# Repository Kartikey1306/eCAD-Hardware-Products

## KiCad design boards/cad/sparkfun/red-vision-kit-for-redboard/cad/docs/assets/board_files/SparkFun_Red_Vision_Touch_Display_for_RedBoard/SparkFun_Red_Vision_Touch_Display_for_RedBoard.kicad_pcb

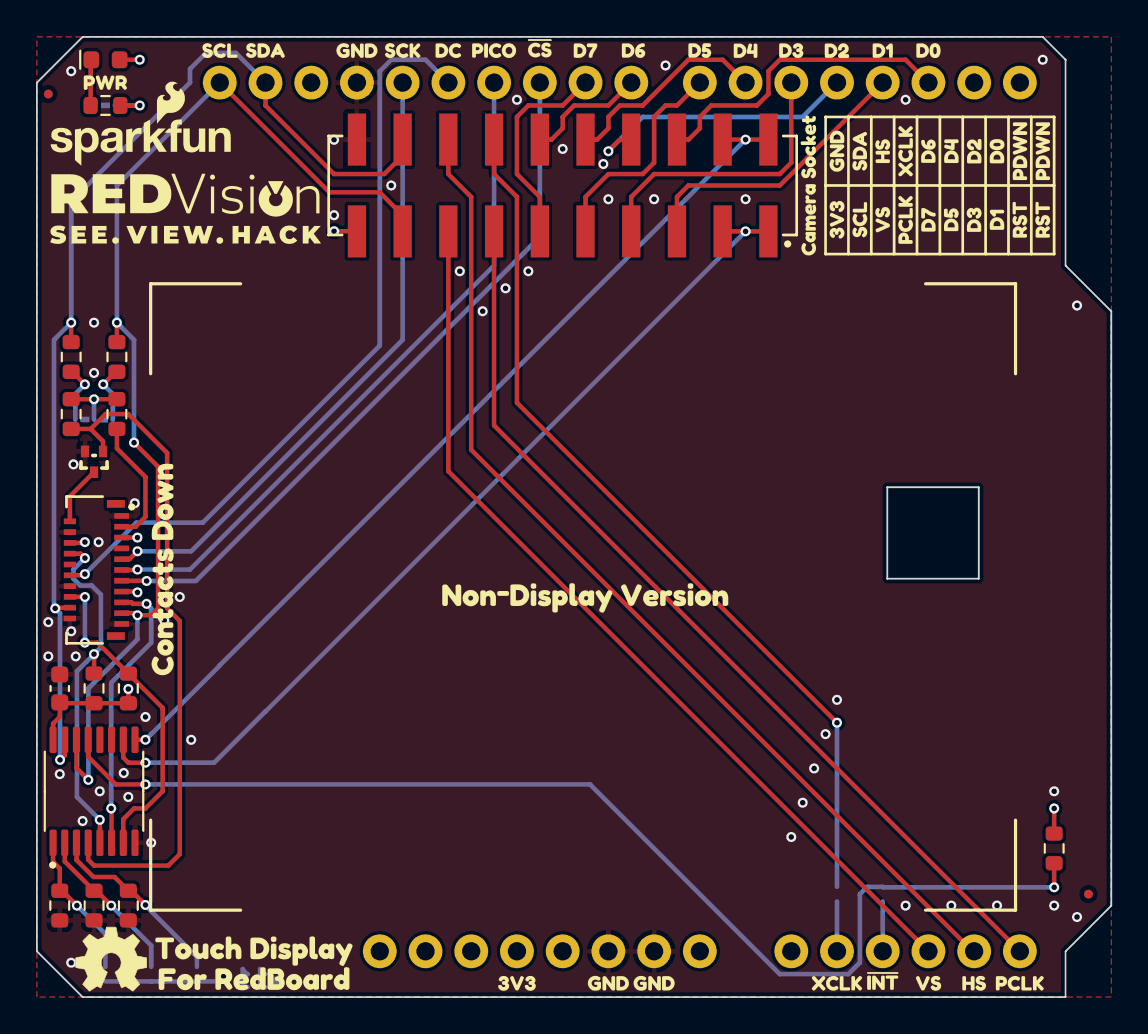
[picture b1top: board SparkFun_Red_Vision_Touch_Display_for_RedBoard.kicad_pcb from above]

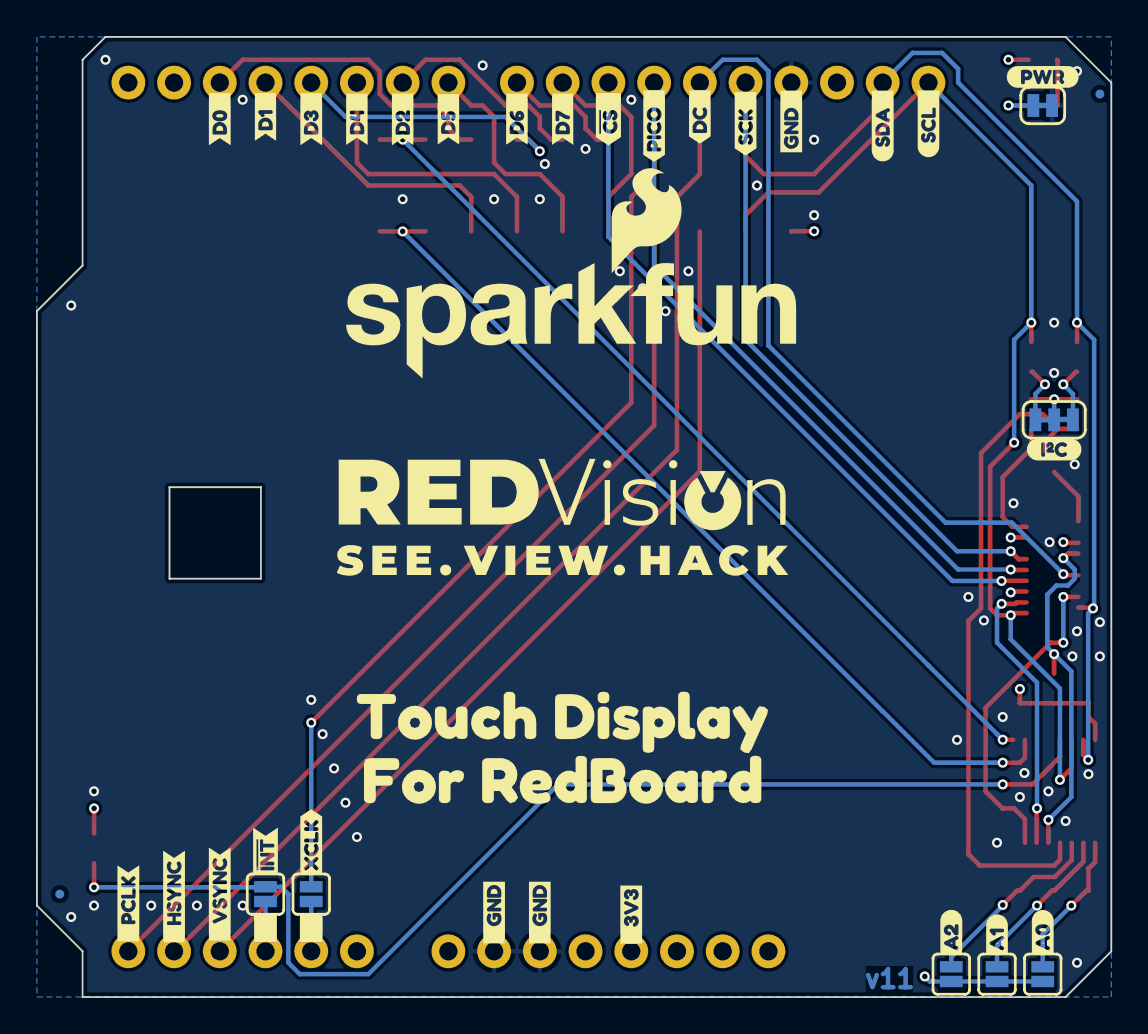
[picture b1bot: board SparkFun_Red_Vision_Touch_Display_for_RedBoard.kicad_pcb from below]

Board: 4 copper layers, 59.7 x 53.3 mm, 111 parts (39 on the bottom side), 38 nets.

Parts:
B1: Arduino_Uno_R3_Shield; Uno_R3_Shield_NoLabels
C2: 0.1uF; C_0603_1608Metric
D1: Red; LED_0603_1608Metric_Red
FID1, FID2, FID3, FID4: Fiducial_0.5mm; Fiducial_0.5mm_Mask1mm
G3: OSHW_Logo; Creative_Commons_License
J1: Conn_02x10_2.54mm_SMD; 2x10_P2.54mm_Socket_Vertical_SMD
J4: Conn_01x21_FPC; FPC_1x21_P0.3mm_Horizontal_DualContact
JP1: I2C; Jumper_3_NC-2_Trace
JP13: XCLK; Jumper_2_NO
JP14: A0; Jumper_2_NO
JP15: A1; Jumper_2_NO
JP16: A2; Jumper_2_NO
JP21: PWR; Jumper_2_NC_Trace
JP22: ~{INT}; Jumper_2_NO
Q1: RE1C002UNTCL; SC-89 SOT-490
R1: 10; R_0603_1608Metric
R2, R6, R7, R8, R9, R11, R12: 100k; R_0603_1608Metric
R3, R4: 2.2k; R_0603_1608Metric
R5: 4.7k; R_0603_1608Metric
Ref**: Val**; OSHW_Logo_4mm
U1: 2" LCD-TFT 240x320; LCD_TFT_2.0in_Waveshare_Outline
U2: PCA9534PW; TSSOP-16_4.4x5mm_P0.65mm
kibuzzard-67A69C5F, kibuzzard-67A69C5F#2: G***; kibuzzard-67A69C5F
kibuzzard-67A69CD2, kibuzzard-67A69CD2#2: G***; kibuzzard-67A69CD2
kibuzzard-67A69CDC: G***; kibuzzard-67A69CDC
kibuzzard-67A69CE2: G***; kibuzzard-67A69CE2
kibuzzard-67A69CE6: G***; kibuzzard-67A69CE6
kibuzzard-67A69CEA: G***; kibuzzard-67A69CEA
kibuzzard-67A69CFF: G***; kibuzzard-67A69CFF
kibuzzard-67A69D0C: G***; kibuzzard-67A69D0C
kibuzzard-67A69D0F: G***; kibuzzard-67A69D0F
kibuzzard-67A69D1B: G***; kibuzzard-67A69D1B
kibuzzard-67A69D2C: G***; kibuzzard-67A69D2C
kibuzzard-67A69D2F: G***; kibuzzard-67A69D2F
kibuzzard-67A69D05: G***; kibuzzard-67A69D05
kibuzzard-67A69D16: G***; kibuzzard-67A69D16
kibuzzard-67A69D28: G***; kibuzzard-67A69D28
kibuzzard-67A69D32: G***; kibuzzard-67A69D32
kibuzzard-67A69E51: G***; kibuzzard-67A69E51
kibuzzard-67A69E55: G***; kibuzzard-67A69E55
kibuzzard-67B3FFE0: G***; kibuzzard-67B3FFE0
kibuzzard-67C124A5: G***; kibuzzard-67C124A5
kibuzzard-67C1248C: G***; kibuzzard-67C1248C
kibuzzard-68B0C822: G***; kibuzzard-68B0C822
kibuzzard-68B0C855: G***; kibuzzard-68B0C855
kibuzzard-68B1DD36: G***; kibuzzard-68B1DD36
kibuzzard-68B9B772: G***; kibuzzard-68B9B772
kibuzzard-68B9BC57: G***; kibuzzard-68B9BC57
kibuzzard-68B9BC59: G***; kibuzzard-68B9BC59
kibuzzard-68B9BC63: G***; kibuzzard-68B9BC63
kibuzzard-68B9BCE4: G***; kibuzzard-68B9BCE4
kibuzzard-68B9BCEA: G***; kibuzzard-68B9BCEA
kibuzzard-68B9BCF4: G***; kibuzzard-68B9BCF4
kibuzzard-68B9BD3D: G***; kibuzzard-68B9BD3D
kibuzzard-68B9BD4B: G***; kibuzzard-68B9BD4B
kibuzzard-68B9BD7F: G***; kibuzzard-68B9BD7F
kibuzzard-68B9BD9B: G***; kibuzzard-68B9BD9B
kibuzzard-68B9BD55: G***; kibuzzard-68B9BD55
kibuzzard-68B9BD76: G***; kibuzzard-68B9BD76
kibuzzard-68B9BDA0: G***; kibuzzard-68B9BDA0
kibuzzard-68B9BDA7: G***; kibuzzard-68B9BDA7
kibuzzard-68B9BDC0: G***; kibuzzard-68B9BDC0
kibuzzard-68B9BDC6: G***; kibuzzard-68B9BDC6
kibuzzard-68B9BDCB: G***; kibuzzard-68B9BDCB
kibuzzard-68B9BE6E: G***; kibuzzard-68B9BE6E
kibuzzard-68B9BE9E: G***; kibuzzard-68B9BE9E
kibuzzard-68B9BE85: G***; kibuzzard-68B9BE85
kibuzzard-68B9BE89: G***; kibuzzard-68B9BE89
kibuzzard-68B9BEAF: G***; kibuzzard-68B9BEAF
kibuzzard-68B9BECE, kibuzzard-68B9BECE#2: G***; kibuzzard-68B9BECE
kibuzzard-68B9BED6: G***; kibuzzard-68B9BED6
kibuzzard-68B9BEDF: G***; kibuzzard-68B9BEDF
kibuzzard-68B9BEFF: G***; kibuzzard-68B9BEFF
kibuzzard-68B9BF01: G***; kibuzzard-68B9BF01
kibuzzard-68B9BF2B: G***; kibuzzard-68B9BF2B
kibuzzard-68B9BF3C: G***; kibuzzard-68B9BF3C
kibuzzard-68B9BF4D: G***; kibuzzard-68B9BF4D
kibuzzard-68B9BF5D: G***; kibuzzard-68B9BF5D
kibuzzard-68B9BF06: G***; kibuzzard-68B9BF06
kibuzzard-68B9BF8B: G***; kibuzzard-68B9BF8B
kibuzzard-68B9BF11: G***; kibuzzard-68B9BF11
kibuzzard-68B9BF14: G***; kibuzzard-68B9BF14
kibuzzard-68B9BF19: G***; kibuzzard-68B9BF19
kibuzzard-68B9BF49: G***; kibuzzard-68B9BF49
kibuzzard-68B9BF52: G***; kibuzzard-68B9BF52
kibuzzard-68B9BF61: G***; kibuzzard-68B9BF61
kibuzzard-68B9BF65: G***; kibuzzard-68B9BF65
kibuzzard-68B9BF69: G***; kibuzzard-68B9BF69
kibuzzard-68B202D3: G***; kibuzzard-68B202D3
kibuzzard-68B202D8: G***; kibuzzard-68B202D8
kibuzzard-68EEA4F5: G***; kibuzzard-68EEA4F5
kibuzzard-68EEA4FB: G***; kibuzzard-68EEA4FB
kibuzzard-68EEA50D: G***; kibuzzard-68EEA50D
kibuzzard-68EEA51B: G***; kibuzzard-68EEA51B
kibuzzard-68EEA508: G***; kibuzzard-68EEA508
kibuzzard-68EEA511: G***; kibuzzard-68EEA511
kibuzzard-68EEA516: G***; kibuzzard-68EEA516
kibuzzard-68EEA520: G***; kibuzzard-68EEA520

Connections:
3.3V: B1.3.3V, C2.1, D1.2 (A), J1.19, J4.5, J4.6, J4.15, JP1.2 (B), JP14.2 (B), JP15.2 (B), JP16.2 (B), R1.2, R2.2, R6.2, R11.2, R12.2, U2.16 (VDD)
A0: JP14.1 (A), R7.2, U2.1 (A0)
A1: JP15.1 (A), R8.2, U2.2 (A1)
A2: JP16.1 (A), R9.2, U2.3 (A2)
CAM_D0: B1.D2, J1.6
CAM_D1: B1.D3 (*D3), J1.5
CAM_D2: B1.D4, J1.8
CAM_D3: B1.D5 (*D5), J1.7
CAM_D4: B1.D6 (*D6), J1.10
CAM_D5: B1.D7, J1.9
CAM_D6: B1.D8, J1.12
CAM_D7: B1.D9 (*D9), J1.11
CAM_HS: B1.A4, J1.16
CAM_PCLK: B1.A5, J1.13
CAM_PWDN: J1.2, J1.4, U2.9 (IO4)
CAM_RST: J1.1, J1.3, U2.10 (IO5)
CAM_VS: B1.A3, J1.15
CAM_XCLK: J1.14, JP13.1 (A)
DISP_BL: Q1.1 (G), R2.1, U2.4 (IO0)
DISP_~CS: B1.D10 (*D10), J4.13
DISP_~RST: J4.8, R12.1, U2.5 (IO1)
GND: B1.GND, C2.2, J1.20, J4.1, J4.4, J4.7, J4.14, J4.20, J4.21, JP21.2 (B), Q1.2 (S), R7.1, R8.1, R9.1, U2.8 (VSS)
unnamed: D1.1 (K), R5.2
unnamed: J4.2, Q1.3 (D)
unnamed: J4.3, R1.1
unnamed: JP1.1 (A), R4.1
unnamed: JP1.3 (C), R3.2
unnamed: B1.A1, JP13.2 (B)
unnamed: JP21.1 (A), R5.1
unnamed: B1.A2, JP22.2 (B)
PICO: B1.D11 (*D11/PICO), J4.11
POCI/DC: B1.D12 (D12/POCI), J4.12
SCK: B1.D13 (D13/SCK), J4.9
SCL: B1.SCL, J1.17, J4.19, R4.2, U2.14 (SCL)
SDA: B1.SDA, J1.18, J4.18, R3.1, U2.15 (SDA)
TP_INT: J4.17, U2.6 (IO2)
TP_~RST: J4.16, R11.1, U2.7 (IO3)
~INT: JP22.1 (A), R6.1, U2.13 (~INT)

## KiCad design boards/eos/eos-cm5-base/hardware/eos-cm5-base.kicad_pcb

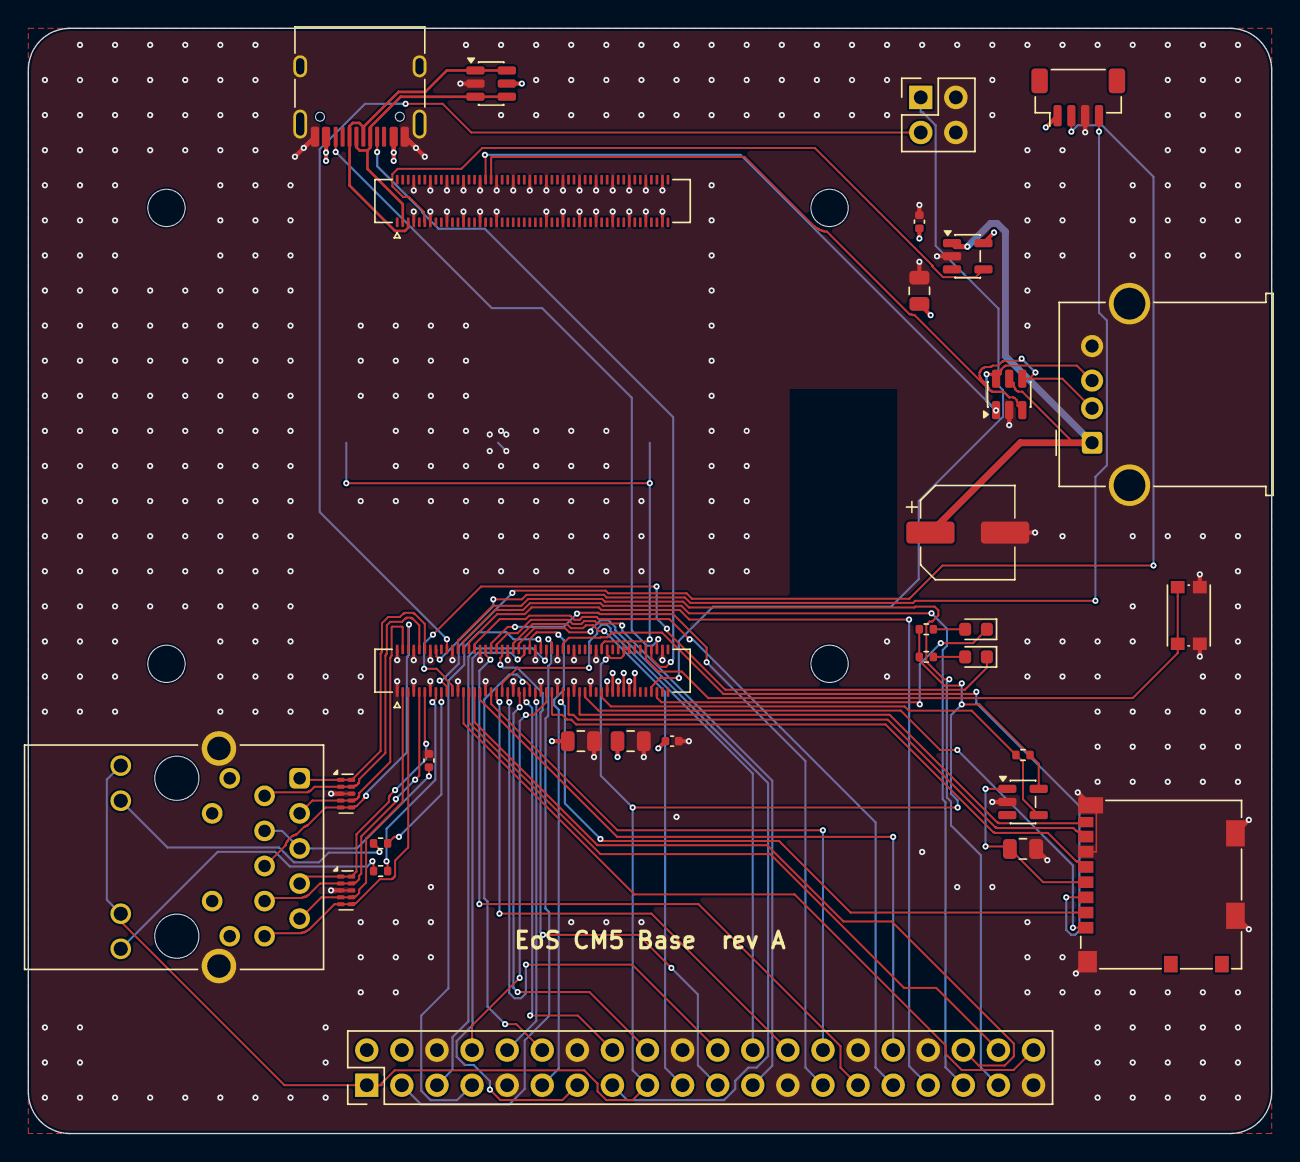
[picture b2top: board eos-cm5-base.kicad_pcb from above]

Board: 4 copper layers, 90.0 x 80.0 mm, 36 parts (1 on the bottom side), 70 nets.

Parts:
BT1: CR2032; BatteryHolder_Keystone_3034_1x20mm
C1, C2, C5, C8: 10u; C_0805_2012Metric
C3, C4, C7: 100n; C_0402_1005Metric
C6: 150u; CP_Elec_6.3x5.8
D1: PWR; LED_0603_1608Metric
D2: ACT; LED_0603_1608Metric
H1, H2, H3, H4: M2.5; MountingHole_2.7mm_M2.5
J1: CM5 1-100; Hirose_DF40C-100DS-0.4V_2x50_P0.4mm
J2: CM5 101-200; Hirose_DF40C-100DS-0.4V_2x50_P0.4mm
J3: USB-C; USB_C_Receptacle_HRO_TYPE-C-31-M-12
J4: USB-A; USB_A_Molex_67643_Horizontal
J5: TRJG0926HENL; TRXCOM_TRJG0926HENL
J6: microSD; microSD_HC_Molex_104031-0811
J7: GPIO; PinHeader_2x20_P2.54mm_Vertical
J8: FAN; JST_SH_BM04B-SRSS-TB_1x04-1MP_P1.00mm_Vertical
J9: BOOT; PinHeader_2x02_P2.54mm_Vertical
R1, R2: 470; R_0402_1005Metric
R3: 10k; R_0402_1005Metric
R4, R5: 1k; R_0402_1005Metric
SW1: POWER; SW_Push_1P1T_NO_CK_KMR2
U1, U3: USBLC6-2SC6; SOT-23-6
U2: TPS2051C; SOT-23-5
U4, U5: TPD4EUSB30; USON-10_2.5x1.0mm_P0.5mm
U6: RT9742GGJ5; TSOT-23-5

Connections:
+3V3: J1.78, J1.84, J1.86, J5.15, J5.17, J7.1, J7.17, R3.2, R4.1, R5.1, U6.5
+5V: C1.1, C2.1, C3.1, C4.1, C5.1, J1.77, J1.79, J1.81, J1.83, J1.85, J1.87, J3.A4, J3.A9, J3.B4, J3.B9, J7.2, J7.4, J8.1, U1.5, U2.5
/CC1: J1.94, J3.A5
/CC2: J1.96, J3.B5
/EEPROM_NWP: J1.20, J9.3
/ETH_A_N: J1.10, J5.2, U4.2, U4.9
/ETH_A_P: J1.12, J5.1, U4.1, U4.10
/ETH_B_N: J1.6, J5.6, U4.5, U4.6
/ETH_B_P: J1.4, J5.3, U4.4, U4.7
/ETH_CT: C7.1, J5.4, J5.5
/ETH_C_N: J1.9, J5.8, U5.2, U5.9
/ETH_C_P: J1.11, J5.7, U5.1, U5.10
/ETH_D_N: J1.5, J5.10, U5.5, U5.6
/ETH_D_P: J1.3, J5.9, U5.4, U5.7
/ETH_LEDG_K: J5.18, R2.1
/ETH_LEDY_K: J5.16, R1.1
/ETH_NLED_ACT: J1.15, R2.2
/ETH_NLED_SPD: J1.17, R1.2
/FAN_PWM: J1.19, J8.2
/FAN_TACHO: J1.16, J8.4
/GPIO2: J1.58, J7.3
/GPIO3: J1.56, J7.5
/GPIO4: J1.54, J7.7
/GPIO5: J1.34, J7.29
/GPIO6: J1.30, J7.31
/GPIO7: J1.37, J7.26
/GPIO8: J1.39, J7.24
/GPIO9: J1.40, J7.21
/GPIO10: J1.44, J7.19
/GPIO11: J1.38, J7.23
/GPIO12: J1.31, J7.32
/GPIO13: J1.28, J7.33
/GPIO14: J1.55, J7.8
/GPIO15: J1.51, J7.10
/GPIO16: J1.29, J7.36
/GPIO17: J1.50, J7.11
/GPIO18: J1.49, J7.12
/GPIO19: J1.26, J7.35
/GPIO20: J1.27, J7.38
/GPIO21: J1.25, J7.40
/GPIO22: J1.46, J7.15
/GPIO23: J1.47, J7.16
/GPIO24: J1.45, J7.18
/GPIO25: J1.41, J7.22
/GPIO26: J1.24, J7.37
/GPIO27: J1.48, J7.13
/ID_SC: J1.35, J7.28
/ID_SD: J1.36, J7.27
/LED_ACT_A: D2.2, R5.2
/LED_NACT: D2.1, J1.21
/LED_NPWR: D1.1, J1.95
/LED_PWR_A: D1.2, R4.2
/NRPIBOOT: J1.93, J9.1
/PWR_BUTTON: J1.92, SW1.1
/SD_CLK: J1.57, J6.5
/SD_CMD: J1.62, J6.3
/SD_DAT0: J1.63, J6.7
/SD_DAT1: J1.67, J6.8
/SD_DAT2: J1.69, J6.1
/SD_DAT3: J1.61, J6.2
/SD_PWR_ON: J1.75, R3.1, U6.4
/SD_VDD: C8.1, J6.4, U6.1
/USBH_DM: J2.36, J4.2, U3.3, U3.4
/USBH_DP: J2.34, J4.3, U3.1, U3.6
/USBH_VBUS: C6.1, J4.1, U2.1, U3.5
/USB_N: J2.3, J3.A7, J3.B7, U1.3, U1.4
/USB_P: J2.5, J3.A6, J3.B6, U1.1, U1.6
/VBAT: BT1.1, J1.76
/VBUS_EN: J2.11, U2.4
GND: BT1.2, C1.2, C2.2, C3.2, C4.2, C5.2, C6.2, C7.2, C8.2, J1.1, J1.2, J1.7, J1.8, J1.13, J1.14, J1.22, J1.23, J1.32, J1.33, J1.42, J1.43, J1.52, J1.53, J1.59, J1.60, J1.65, J1.66, J1.71, J1.74, J1.98, J2.7, J2.8, J2.13, J2.14, J2.19, J2.20, J2.25, J2.26, J2.31, J2.32, J2.37, J2.38, J2.44, J2.50, J2.55, J2.56, J2.61, J2.62, J2.67, J2.68, J2.73, J2.74, J2.79, J2.80, J2.85, J2.86, J2.91, J2.92, J2.97, J2.98, J3.A1, J3.A12, J3.B1, J3.B12, J3.SH, J4.4, J4.SH, J5.19, J5.20, J6.6, J6.SH, J7.6, J7.9, J7.14, J7.20, J7.25, J7.30, J7.34, J7.39, J8.3, J9.2, J9.4, SW1.2, U1.2, U2.2, U3.2, U4.3, U4.8, U5.3, U5.8, U6.2

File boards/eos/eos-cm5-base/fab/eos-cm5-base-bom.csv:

"Refs","Value","Footprint","Manufacturer","MPN","Description","Qty","DNP"
"BT1","CR2032","Battery:BatteryHolder_Keystone_3034_1x20mm","Keystone","3034","Coin cell holder, RTC (VBAT); keep RTC charging off with a CR2032","1",""
"C1,C2,C5,C8","10u","Capacitor_SMD:C_0805_2012Metric","","","Capacitor 10 uF 10 V X5R 0805 (5 V at the module),Capacitor 10 uF 10 V X5R 0805 (TPS2051C input, 1-22 uF per TI),Capacitor 10 uF 10 V X5R 0805 (microSD supply, as CM5IO)","4",""
"C3,C4,C7","100n","Capacitor_SMD:C_0402_1005Metric","","","Capacitor 100 nF X7R 0402 (5 V at the module),Capacitor 100 nF X7R 0402 (MagJack centre tap, as CM5IO),Capacitor 100 nF X7R 0402 (TPS2051C input, as TI specifies)","3",""
"C6","150u","Capacitor_SMD:CP_Elec_6.3x5.8","Panasonic","EEE-FK1A151P","Capacitor 150 uF 10 V aluminium, 6.3 x 5.8 mm (USB host port: 120 uF minimum per TI)","1",""
"D1","PWR","LED_SMD:LED_0603_1608Metric","Kingbright","APTD1608LSURCK","LED red 0603, power (LED_nPWR)","1",""
"D2","ACT","LED_SMD:LED_0603_1608Metric","Kingbright","APTD1608LCGCK","LED green 570 nm 0603, activity (LED_nACT)","1",""
"J1","CM5 1-100","Connector_Hirose_DF40:Hirose_DF40C-100DS-0.4V_2x50_P0.4mm","Amphenol","10164227-1001A1RLF","CM5 connector, pins 1-100, 1.5 mm stacking","1",""
"J2","CM5 101-200","Connector_Hirose_DF40:Hirose_DF40C-100DS-0.4V_2x50_P0.4mm","Amphenol","10164227-1001A1RLF","CM5 connector, pins 101-200, 1.5 mm stacking","1",""
"J3","USB-C","Connector_USB:USB_C_Receptacle_HRO_TYPE-C-31-M-12","Korean Hroparts","TYPE-C-31-M-12","USB-C 2.0 receptacle (power in, USB device)","1",""
"J4","USB-A","Connector_USB:USB_A_Molex_67643_Horizontal","Molex","67643-0910","USB-A receptacle, USB 2.0 host","1",""
"J5","TRJG0926HENL","EoS_Connectors:TRXCOM_TRJG0926HENL","TRXCOM","TRJG0926HENL","RJ45 MagJack 10/100/1000, LEDs (pins as on Raspberry Pi's CM5IO)","1",""
"J6","microSD","Connector_Card:microSD_HC_Molex_104031-0811","Molex","104031-0811","microSD socket (CM5 Lite)","1",""
"J7","GPIO","Connector_PinHeader_2.54mm:PinHeader_2x20_P2.54mm_Vertical","","","Raspberry Pi 40-pin GPIO header","1",""
"J8","FAN","Connector_JST:JST_SH_BM04B-SRSS-TB_1x04-1MP_P1.00mm_Vertical","JST","BM04B-SRSS-TB","Fan: 1 5 V, 2 PWM, 3 GND, 4 tacho","1",""
"J9","BOOT","Connector_PinHeader_2.54mm:PinHeader_2x02_P2.54mm_Vertical","","","Jumpers: 1-2 nRPIBOOT (USB boot), 3-4 EEPROM write protect","1",""
"R1,R2","470","Resistor_SMD:R_0402_1005Metric","","","Resistor 470 ohm 1% 0402 (green LED, activity),Resistor 470 ohm 1% 0402 (yellow LED, speed)","2",""
"R3","10k","Resistor_SMD:R_0402_1005Metric","","","Resistor 10 kohm 1% 0402 (SD_PWR_ON pull-up, as CM5IO)","1",""
"R4,R5","1k","Resistor_SMD:R_0402_1005Metric","","","Resistor 1 kohm 1% 0402 (activity LED, as CM5IO),Resistor 1 kohm 1% 0402 (power LED, as CM5IO)","2",""
"SW1","POWER","Button_Switch_SMD:SW_Push_1P1T_NO_CK_KMR2","C&K","KMR221G LFS","Power button (PWR_Button)","1",""
"U1,U3","USBLC6-2SC6","Package_TO_SOT_SMD:SOT-23-6","STMicroelectronics","USBLC6-2SC6","USB ESD protection,USB ESD protection (host port)","2",""
"U2","TPS2051C","Package_TO_SOT_SMD:SOT-23-5","Texas Instruments","TPS2051CDBVR","USB power switch 0.5 A, enable high","1",""
"U4,U5","TPD4EUSB30","Package_SON:USON-10_2.5x1.0mm_P0.5mm","Texas Instruments","TPD4EUSB30DQAR","ESD protection, Ethernet pairs A and B, flow-through as TI lays it out,ESD protection, Ethernet pairs C and D, flow-through as TI lays it out","2",""
"U6","RT9742GGJ5","Package_TO_SOT_SMD:TSOT-23-5","Richtek","RT9742GGJ5","Load switch for the microSD supply, enable high (as CM5IO)","1",""

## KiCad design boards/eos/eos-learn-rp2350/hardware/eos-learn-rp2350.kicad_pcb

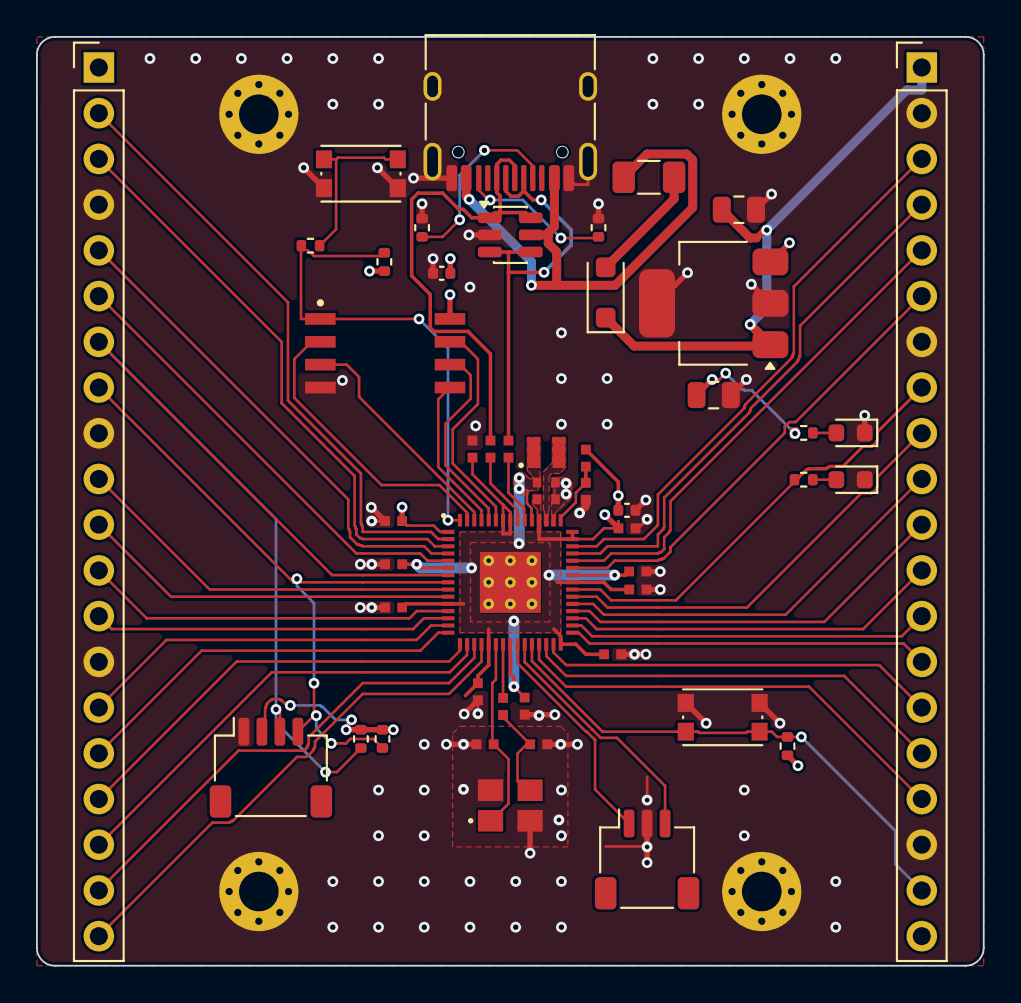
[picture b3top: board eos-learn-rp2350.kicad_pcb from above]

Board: 4 copper layers, 52.6 x 51.6 mm, 53 parts (0 on the bottom side), 59 nets.

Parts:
C1, C2: 10u; C_0805_2012Metric
C3, C4: 15p; generic_capc1005x50
C6, C7: 4.7u; generic_capc1005x50_wide
C9: 4.7u; generic_capc1005x50
C10, C11, C12, C13, C14, C15, C16, C18, C19, C20: 100n; generic_capc1005x50
C17, C21: 100n; C_0402_1005Metric
D1: MBR120VLSFT1G; D_SOD-123F
D2: PWR; LED_0603_1608Metric
D3: GP25; LED_0603_1608Metric
F1: 500mA; Fuse_1206_3216Metric
H1, H2, H3, H4: M2; MountingHole_2.2mm_M2_Pad_Via
J1: USB-C; USB_C_Receptacle_HRO_TYPE-C-31-M-12
J2: GPIO 0-15; PinHeader_1x20_P2.54mm_Vertical
J3: Power, GPIO 16-29; PinHeader_1x20_P2.54mm_Vertical
J4: SWD; JST_SH_SM03B-SRSS-TB_1x03-1MP_P1.00mm_Horizontal
J5: Qwiic; JST_SH_SM04B-SRSS-TB_1x04-1MP_P1.00mm_Horizontal
L1: 3.3u; abracon_aota-b201610s3r3-101-t
R1, R2: 5.1k; R_0402_1005Metric
R3, R4: 27; generic_resc1005x35
R5, R8: 1k; R_0402_1005Metric
R6: 33; generic_resc1005x35
R7, R9: 10k; R_0402_1005Metric
R10: 1k; generic_resc1005x35
R11: 470; R_0402_1005Metric
R12, R13: 4.7k; R_0402_1005Metric
SW1: BOOTSEL; SW_Push_1P1T_NO_CK_KMR2
SW2: RUN; SW_Push_1P1T_NO_CK_KMR2
U1: RP2350A; rpi_rp2350a_vias
U2: USBLC6-2SC6; SOT-23-6
U3: AP7361C-33; SOT-223-3_TabPin2
U4: W25Q128JVS; generic_soic127p790x195-8
Y1: 12MHz; generic_xtalcc320x250x80-4

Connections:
+1V1: C7.1, C18.1, C19.1, C20.1, L1.1, U1.6 (DVDD), U1.23 (DVDD), U1.39 (DVDD), U1.50 (VREG_FB)
+3V3: C2.1, C6.1, C10.1, C11.1, C12.1, C13.1, C14.1, C15.1, C16.1, C17.1, C21.1, J2.1, J3.20, J5.2, R5.1, R6.1, R7.2, R9.2, R12.2, R13.2, U1.1 (IOVDD), U1.11 (IOVDD), U1.20 (IOVDD), U1.30 (IOVDD), U1.38 (IOVDD), U1.44 (ADC_AVDD), U1.45 (IOVDD), U1.49 (VREG_VIN), U1.53 (USB_OTP_VDD), U1.54 (QSPI_IOVDD), U3.3, U4.8 (VCC)
+5V: C1.1, D1.1, J3.1, U3.1
/BOOTSEL: R8.2, SW1.1
/CC1: J1.A5, R1.1
/CC2: J1.B5, R2.1
/GPIO0: J2.2, U1.2 (GPIO0)
/GPIO1: J2.3, U1.3 (GPIO1)
/GPIO2: J2.5, U1.4 (GPIO2)
/GPIO3: J2.6, U1.5 (GPIO3)
/GPIO4: J2.7, J5.3, R12.1, U1.7 (GPIO4)
/GPIO5: J2.8, J5.4, R13.1, U1.8 (GPIO5)
/GPIO6: J2.10, U1.9 (GPIO6)
/GPIO7: J2.11, U1.10 (GPIO7)
/GPIO8: J2.12, U1.12 (GPIO8)
/GPIO9: J2.13, U1.13 (GPIO9)
/GPIO10: J2.15, U1.14 (GPIO10)
/GPIO11: J2.16, U1.15 (GPIO11)
/GPIO12: J2.17, U1.16 (GPIO12)
/GPIO13: J2.18, U1.17 (GPIO13)
/GPIO14: J2.19, U1.18 (GPIO14)
/GPIO15: J2.20, U1.19 (GPIO15)
/GPIO16: J3.17, U1.27 (GPIO16)
/GPIO17: J3.16, U1.28 (GPIO17)
/GPIO18: J3.15, U1.29 (GPIO18)
/GPIO19: J3.14, U1.31 (GPIO19)
/GPIO20: J3.13, U1.32 (GPIO20)
/GPIO21: J3.12, U1.33 (GPIO21)
/GPIO22: J3.11, U1.34 (GPIO22)
/GPIO23: J3.10, U1.35 (GPIO23)
/GPIO24: J3.9, U1.36 (GPIO24)
/GPIO25: J3.8, R11.1, U1.37 (GPIO25)
/GPIO26_ADC0: J3.6, U1.40 (GPIO26_ADC0)
/GPIO27_ADC1: J3.5, U1.41 (GPIO27_ADC1)
/GPIO28_ADC2: J3.4, U1.42 (GPIO28_ADC2)
/GPIO29_ADC3: J3.3, U1.43 (GPIO29_ADC3)
/LED_PWR_A: D2.2, R5.2
/LED_USR_A: D3.2, R11.2
/QSPI_SCLK: U1.56 (QSPI_SCLK), U4.6 (CLK)
/QSPI_SD0: U1.57 (QSPI_SD0), U4.5 (DI_IO0)
/QSPI_SD1: U1.59 (QSPI_SD1), U4.2 (DO_IO1)
/QSPI_SD2: U1.58 (QSPI_SD2), U4.3 (~WP_IO2)
/QSPI_SD3: U1.55 (QSPI_SD3), U4.7 (~HOLD_IO3)
/QSPI_SS: R7.1, R8.1, U1.60 (QSPI_~SS), U4.1 (~CS)
/RP_USB_DM: R4.2, U1.51 (USB_DM)
/RP_USB_DP: R3.2, U1.52 (USB_DP)
/RUN: J3.19, R9.1, SW2.1, U1.26 (RUN)
/SWCLK: J4.1, U1.24 (SWCLK)
/SWDIO: J4.3, U1.25 (SWDIO)
/USB_D+: J1.A6, J1.B6, R3.1, U2.1, U2.6
/USB_D-: J1.A7, J1.B7, R4.1, U2.3, U2.4
/VBUS_F: D1.2, F1.2
/VREG_AVDD: C9.1, R6.2, U1.46 (VREG_AVDD)
/VREG_LX: L1.2, U1.48 (VREG_LX)
/XIN: C3.1, U1.21 (XIN), Y1.1
/XOUT: R10.1, U1.22 (XOUT)
/XTAL_OUT: C4.1, R10.2, Y1.3
GND: C1.2, C2.2, C3.2, C4.2, C6.2, C7.2, C9.2, C10.2, C11.2, C12.2, C13.2, C14.2, C15.2, C16.2, C17.2, C18.2, C19.2, C20.2, C21.2, D2.1, D3.1, H1.1, H2.1, H3.1, H4.1, J1.A1, J1.A12, J1.B1, J1.B12, J1.SH, J2.4, J2.9, J2.14, J3.2, J3.7, J3.18, J4.2, J5.1, R1.2, R2.2, SW1.2, SW2.2, U1.47 (VREG_PGND), U1.61 (GND), U2.2, U3.2, U4.4 (GND), Y1.2, Y1.4
VBUS: F1.1, J1.A4, J1.A9, J1.B4, J1.B9, U2.5

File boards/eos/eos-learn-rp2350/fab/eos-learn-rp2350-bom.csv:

"Refs","Value","Footprint","Manufacturer","MPN","Description","Qty","DNP"
"C1,C2","10u","Capacitor_SMD:C_0805_2012Metric","","","Capacitor 10 uF 10 V X5R 0805 (LDO input),Capacitor 10 uF 10 V X5R 0805 (LDO output)","2",""
"C3,C4","15p","EoS_RPi_Reference:generic_capc1005x50","","","Capacitor 15 pF C0G 0402 (crystal load)","2",""
"C6,C7","4.7u","EoS_RPi_Reference:generic_capc1005x50_wide","","","Capacitor 4.7 uF X5R 0402 (VREG output),Capacitor 4.7 uF X5R 0402 (VREG_VIN)","2",""
"C9","4.7u","EoS_RPi_Reference:generic_capc1005x50","","","Capacitor 4.7 uF X5R 0402 (VREG_AVDD filter)","1",""
"C10-C16,C18-C20","100n","EoS_RPi_Reference:generic_capc1005x50","","","Capacitor 100 nF X7R 0402 (decoupling)","10",""
"C17,C21","100n","Capacitor_SMD:C_0402_1005Metric","","","Capacitor 100 nF X7R 0402 (decoupling),Capacitor 100 nF X7R 0402 (flash)","2",""
"D1","MBR120VLSFT1G","Diode_SMD:D_SOD-123F","onsemi","MBR120VLSFT1G","Schottky 20 V 1 A, SOD-123FL: 5 V fed into the header cannot reach the USB host","1",""
"D2","PWR","LED_SMD:LED_0603_1608Metric","Kingbright","APTD1608LSURCK","LED red 0603","1",""
"D3","GP25","LED_SMD:LED_0603_1608Metric","Kingbright","APTD1608LCGCK","LED green 570 nm 0603, about 1.9 V at 2 mA","1",""
"F1","500mA","Fuse:Fuse_1206_3216Metric","Littelfuse","1206L050YR","PTC resettable fuse 500 mA hold, 1206","1",""
"J1","USB-C","Connector_USB:USB_C_Receptacle_HRO_TYPE-C-31-M-12","Korean Hroparts","TYPE-C-31-M-12","USB-C 2.0 receptacle, 16 pins, mid-mount","1",""
"J2","GPIO 0-15","Connector_PinHeader_2.54mm:PinHeader_1x20_P2.54mm_Vertical","","","Pin header 1x20 2.54 mm","1",""
"J3","Power, GPIO 16-29","Connector_PinHeader_2.54mm:PinHeader_1x20_P2.54mm_Vertical","","","Pin header 1x20 2.54 mm","1",""
"J4","SWD","Connector_JST:JST_SH_SM03B-SRSS-TB_1x03-1MP_P1.00mm_Horizontal","JST","SM03B-SRSS-TB","SWD: Raspberry Pi Debug Probe pinout","1",""
"J5","Qwiic","Connector_JST:JST_SH_SM04B-SRSS-TB_1x04-1MP_P1.00mm_Horizontal","JST","SM04B-SRSS-TB","Qwiic / STEMMA QT I2C0: SDA GPIO4, SCL GPIO5","1",""
"L1","3.3u","EoS_RPi_Reference:abracon_aota-b201610s3r3-101-t","Abracon","AOTA-B201610S3R3-101-T","Inductor 3.3 uH 2016, polarity-marked; fitted as Raspberry Pi's reference footprint orients it","1",""
"R1,R2","5.1k","Resistor_SMD:R_0402_1005Metric","","","Resistor 5.1k 1% 0402","2",""
"R3,R4","27","EoS_RPi_Reference:generic_resc1005x35","","","Resistor 27 1% 0402","2",""
"R5,R8","1k","Resistor_SMD:R_0402_1005Metric","","","Resistor 1k 1% 0402","2",""
"R6","33","EoS_RPi_Reference:generic_resc1005x35","","","Resistor 33 1% 0402","1",""
"R9","10k","Resistor_SMD:R_0402_1005Metric","","","Resistor 10k 1% 0402","1",""
"R10","1k","EoS_RPi_Reference:generic_resc1005x35","","","Resistor 1k 1% 0402","1",""
"R11","470","Resistor_SMD:R_0402_1005Metric","","","Resistor 470 1% 0402","1",""
"R12,R13","4.7k","Resistor_SMD:R_0402_1005Metric","","","Resistor 4.7k 1% 0402","2",""
"SW1","BOOTSEL","Button_Switch_SMD:SW_Push_1P1T_NO_CK_KMR2","C&K","KMR221G LFS","Tactile switch, BOOTSEL","1",""
"SW2","RUN","Button_Switch_SMD:SW_Push_1P1T_NO_CK_KMR2","C&K","KMR221G LFS","Tactile switch, RUN (reset)","1",""
"U1","RP2350A","EoS_RPi_Reference:rpi_rp2350a_vias","Raspberry Pi","RP2350A0A2","Dual Cortex-M33 / Hazard3 microcontroller, QFN-60","1",""
"U2","USBLC6-2SC6","Package_TO_SOT_SMD:SOT-23-6","STMicroelectronics","USBLC6-2SC6","USB ESD protection","1",""
"U3","AP7361C-33","Package_TO_SOT_SMD:SOT-223-3_TabPin2","Diodes Incorporated","AP7361C-33E-13","LDO 3.3 V 1 A, SOT-223, stable with ceramic capacitors of 2.2 uF or more","1",""
"U4","W25Q128JVS","EoS_RPi_Reference:generic_soic127p790x195-8","Winbond","W25Q128JVSIQ","128 Mbit QSPI NOR flash, SOIC-8 208 mil","1",""
"Y1","12MHz","EoS_RPi_Reference:generic_xtalcc320x250x80-4","Abracon","ABM8-272-T3","Crystal 12 MHz 10 pF 30 ppm, 3225","1",""

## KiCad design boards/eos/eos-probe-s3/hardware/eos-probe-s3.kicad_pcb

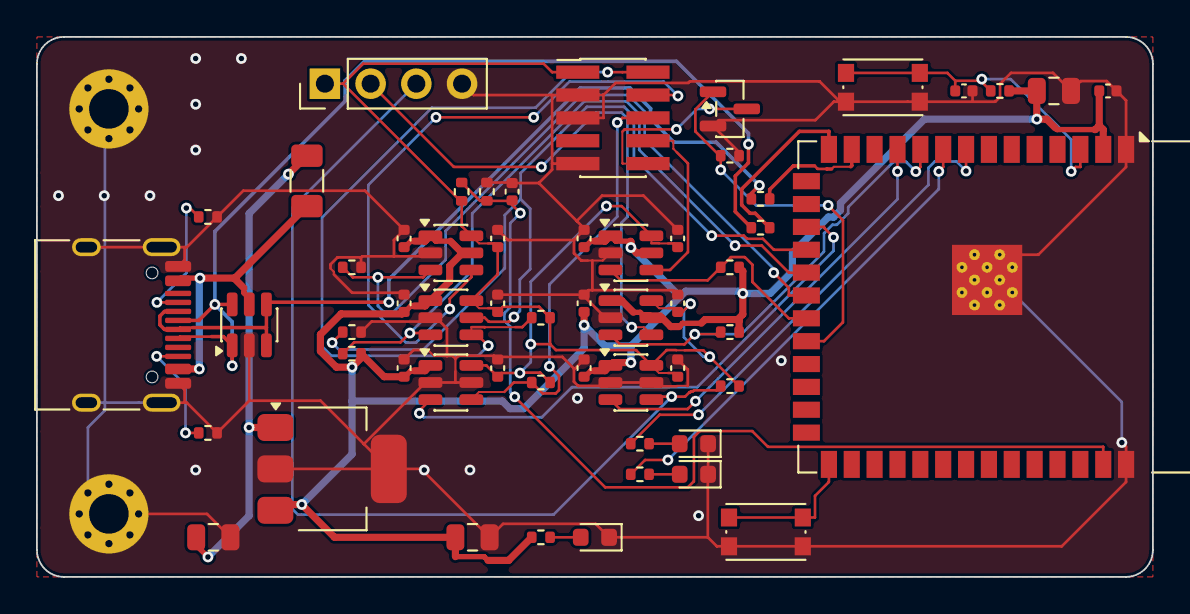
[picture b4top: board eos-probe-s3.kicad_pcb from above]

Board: 2 copper layers, 62.0 x 30.0 mm, 58 parts (0 on the bottom side), 34 nets.

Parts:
C1, C2: 4.7u; C_0805_2012Metric
C3: 22u; C_0805_2012Metric
C4, C6, C7, C8, C9, C10, C11, C12, C13, C14, C15, C16, C17, C18: 100n; C_0402_1005Metric
C5: 1u; C_0402_1005Metric
D1: PWR; LED_0603_1608Metric
D2: STAT; LED_0603_1608Metric
D3: ACT; LED_0603_1608Metric
F1: 500mA; Fuse_1206_3216Metric
H1, H2: M2; MountingHole_2.2mm_M2_Pad_Via
J1: USB-C; USB_C_Receptacle_HRO_TYPE-C-31-M-12
J2: Cortex Debug; PinHeader_2x05_P1.27mm_Vertical_SMD
J3: Target UART; PinHeader_1x04_P2.54mm_Vertical
Q1: 2N7002; SOT-23
R1, R2: 5.1k; R_0402_1005Metric
R3: 1k; R_0402_1005Metric
R4: 10k; R_0402_1005Metric
R5, R6: 0; R_0402_1005Metric
R7, R8: 470; R_0402_1005Metric
R9, R10, R11, R12, R13, R14, R15, R16, R17, R18, R19: 100k; R_0402_1005Metric
SW1: RESET; SW_Push_1P1T_NO_CK_KMR2
SW2: BOOT; SW_Push_1P1T_NO_CK_KMR2
U1: USBLC6-2SC6; SOT-23-6
U2: AP7361C-33; SOT-223-3_TabPin2
U3: ESP32-S3-WROOM-1-N8R2; ESP32-S3-WROOM-1
U4, U5, U6, U7, U8, U9: SN74LVC1T45; SOT-23-6

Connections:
+3V3: C2.1, C3.1, C4.1, C6.1, C7.1, C8.1, C9.1, C10.1, C11.1, R3.1, R4.2, R11.2, R12.2, R13.2, U2.3, U3.2, U4.1, U4.5, U5.1, U6.1, U7.1, U7.5, U8.1, U8.5, U9.1
+5V: C1.1, F1.2, U2.1
/BOOT: SW2.1, U3.27
/CC1: J1.A5, R1.1
/CC2: J1.B5, R2.1
/EN: C5.1, R4.1, SW1.1, U3.3
/ESP_D+: R6.2, U3.14
/ESP_D-: R5.2, U3.13
/LED_ACT: R8.1, U3.9
/LED_ACT_A: D3.2, R8.2
/LED_PWR_A: D1.2, R3.2
/LED_STAT: R7.1, U3.8
/LED_STAT_A: D2.2, R7.2
/NRESET_G: Q1.1, R17.1, U3.22
/SWCLK_A: R9.1, U3.20, U4.3
/SWDIO_A: R11.1, U3.19, U5.3
/SWDIO_DIR: R10.1, U3.18, U5.5
/SWO_A: U3.17, U6.3
/TDI_A: R12.1, U3.21, U7.3
/T_NRESET: J2.10, Q1.3
/T_SWCLK: J2.4, U4.4
/T_SWDIO: J2.2, R14.1, U5.4
/T_SWO: J2.6, R15.1, U6.4
/T_TDI: J2.8, U7.4
/T_UART_RX: J3.3, R16.1, U9.4
/T_UART_TX: J3.2, U8.4
/UART_RX_A: U3.11, U9.3
/UART_TX_A: R13.1, U3.10, U8.3
/USB_D+: J1.A6, J1.B6, R6.1, U1.1, U1.6
/USB_D-: J1.A7, J1.B7, R5.1, U1.3, U1.4
/VTREF: C12.1, C13.1, C14.1, C15.1, C16.1, C17.1, J2.1, J3.1, R14.2, R15.2, R16.2, R18.1, U4.6, U5.6, U6.6, U7.6, U8.6, U9.6
/VTREF_SENSE: C18.1, R18.2, R19.1, U3.39
GND: C1.2, C2.2, C3.2, C4.2, C5.2, C6.2, C7.2, C8.2, C9.2, C10.2, C11.2, C12.2, C13.2, C14.2, C15.2, C16.2, C17.2, C18.2, D1.1, D2.1, D3.1, H1.1, H2.1, J1.A1, J1.A12, J1.B1, J1.B12, J1.SH, J2.3, J2.5, J2.9, J3.4, Q1.2, R1.2, R2.2, R9.2, R10.2, R17.2, R19.2, SW1.2, SW2.2, U1.2, U2.2, U3.1, U3.40, U3.41, U4.2, U5.2, U6.2, U6.5, U7.2, U8.2, U9.2, U9.5
VBUS: F1.1, J1.A4, J1.A9, J1.B4, J1.B9, U1.5

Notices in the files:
boards/eos/eos-cm5-base/hardware/eos-cm5-base.kicad_pcb:
(c) 2026 Kartikeydheer Srivastava
All rights reserved
boards/eos/eos-learn-rp2350/hardware/eos-learn-rp2350.kicad_pcb:
Core layout (c) 2026 Raspberry Pi Ltd  MIT
parts and their libraries:
https://creativecommons.org/licenses/by-sa/4.0
Released under the Creative Commons Attribution Share-Alike 4.0 License
